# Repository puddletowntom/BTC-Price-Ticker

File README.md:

# Bitcoin Metrics Tracker

# WARNING!!

Problems still remain with this project when using Wi-Fi at the same time as LCD. Wi-Fi connection is inconsistent and sometimes fails a HTTP request. 
Another attempt was made in a different project where i failed to get Wi-Fi working at all with display. Both RGB display and Wi-Fi use PSRAM so there is a problem with shared resources. Getting around this may require a change to the hardware. I was thinking of simply using 2 ESP32s with 1 dedicated to RF. Perhaps there is a clever solution around temporarily disabling SPI bus for LCD on Wi-Fi commands or maybe some internal changes around LCD initialisation. Solving this problem has been too time consuming and a more careful design of the hardware would have been better I think. 

# Introduction

The Bitcoin metrics tracker was designed to sit near your desktop and keep an eye on several key important metrics on the Bitcoin network. These metrics include the Bitcoin price, the total Bitcoin marketcap, the total Bitcoin supply, the hash rate of the network, the current number of Bitcoins rewarded per block, the estimated time interval between blocks mined, the number of blocks mined so far and the remaining blocks left to mine in the current 4 year cycle. It uses Wi-Fi to connect to Blockchain.com to update the metrics at regular intervals. There is no need to hard code Wi-Fi credentials as there is a WPS setup for synchronisation with your router. Router credentials are then saved to flash memory via NVS so that you only have to do it one time. The green light on the screen indicates if Wi-Fi is connected. The green light will switch off if disconnected with the router. It will try to reconnect when it disconnects. The spinner around the green light is when the data is updating. 

# Parts Included

For the 3D printed case I have included the 3mf files. This project includes the following,

- RGB (565) display with ST7701s IC driver,
- ESP32-S3 R8 (8MB PSRAM) and 4MB of flash memory,
- Charging circuitry on PCB,
- USB-C,
- 3D print case

# Development Board

# Software 

- Kicad for PCB files,
- Fusion 360 for STL files,
- ESP-IDF for development environment,
- SquareLine Studio for display graphics

# Pinout

You can find the entire pinout with the schematic provided. But a brief overview is as follows,

Buttons

- TP6 to TP7 for Power button,
- SW3 - Reset button,
- SW4 - Boot button

# WPS

When you first turn on the device you will be met with the WPS screen. This is so you can connect to your router without needing to type your Wi-Fi credentials. So you need to press your WPS button on your router to sync it with the device. If it fails to move on from the WPS screen, unplug the device and plug it back in and press the WPS button on the router again. If it syncs with your router it will move on to the next screen which is a Bitcoin logo saying setup. 

# Programming the device

There are two modes for the ESP32-S3, download mode (upload program) and run mode (code running). To put the board in program mode press and hold the button SW4 (boot) and while this is still being held press the SW3 (reset) button. To put the board into run mode just press SW3 (reset) button once or alternatively just unplug the device. 

- idf.py set-target ESP32-S3 (only need to do this once)
- idf.py build (rebuild when you make changes to code)
- idf.py flash -p COM8 -b 921600 monitor (download code while monitoring)

# Restore credentials

If you want to change the Wi-Fi credentials to a new router, I have put in a define for restoring credentials. To do this you need to uncomment the following and build+download+run this code to clear credentials. 

#define CONFIG_RESTORE

You then need to comment it out again and download it to revert to original code. 

//#define CONFIG_RESTORE

# Further Work

The device currently doesnt have a GPIO reset button which means that once you sync the device with a Wi-Fi router via WPS you cant join a different router unless you reprogram the board with the config restore feature.

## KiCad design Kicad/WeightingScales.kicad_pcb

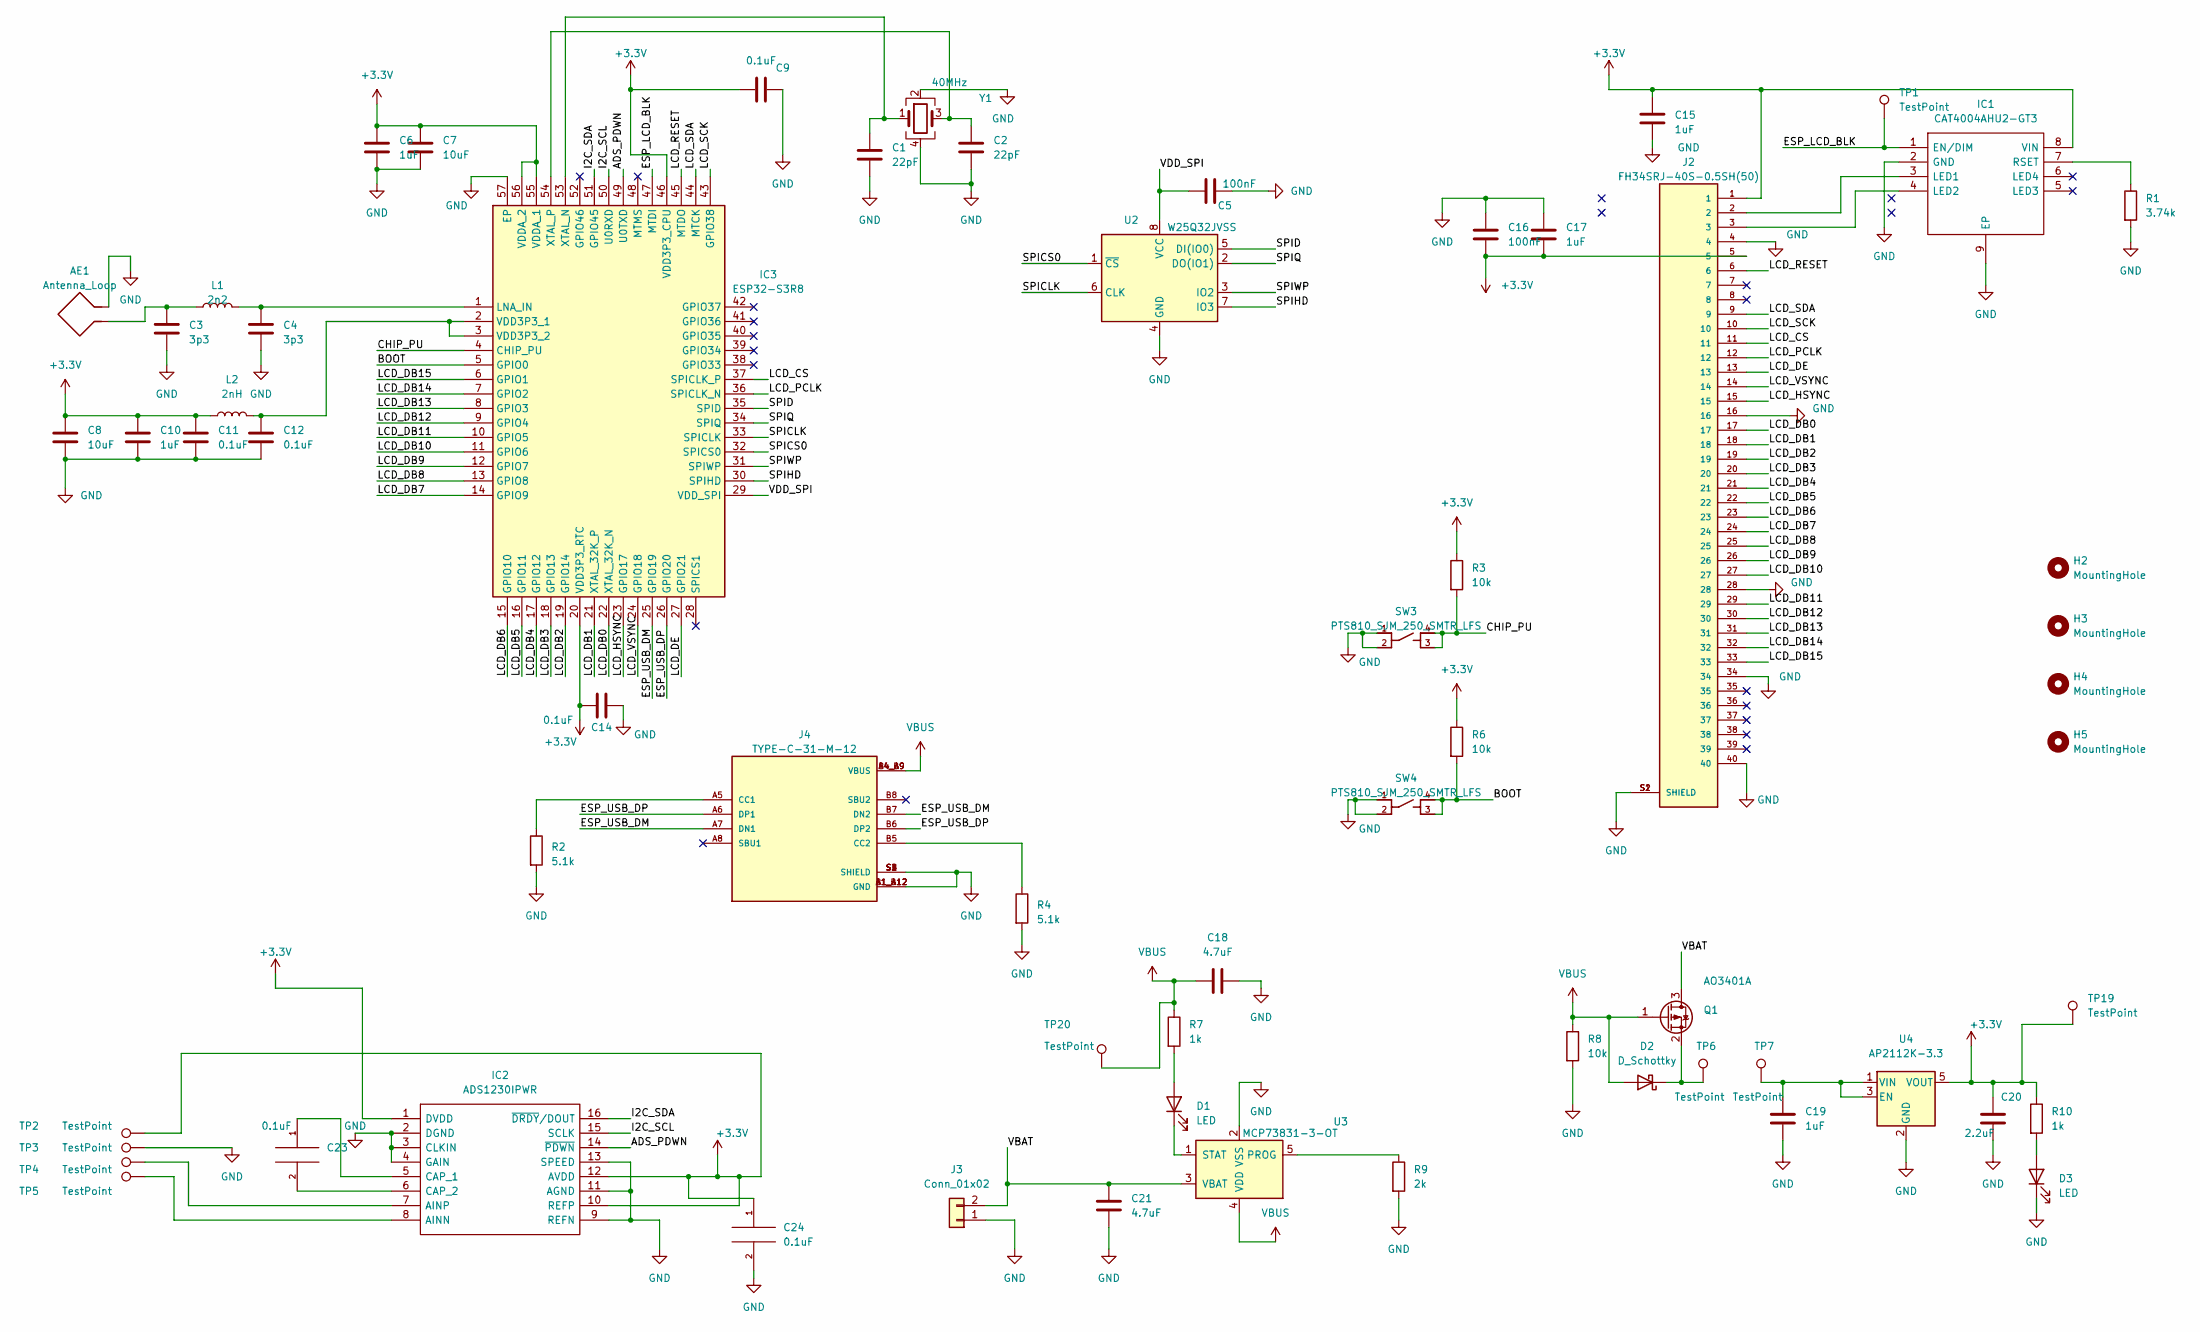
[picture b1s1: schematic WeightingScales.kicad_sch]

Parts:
AE1: Antenna_Loop; ESPRESSIF_ESP32_MIFA_2.4GHz_Right
C1, C2: 22pF; C_0402_1005Metric
C3, C4: 3p3; C_0402_1005Metric
C5, C16: 100nF; C_0402_1005Metric
C6, C10, C17, C19: 1uF; C_0402_1005Metric
C7, C8: 10uF; C_0603_1608Metric
C9, C11, C12, C14, C23, C24: 0.1uF; C_0402_1005Metric
C15: 1uF; C_0805_2012Metric
C18, C21: 4.7uF; C_0603_1608Metric
C20: 2.2uF; C_0402_1005Metric
D1, D3: LED; LED_0603_1608Metric
D2: D_Schottky; D_0603_1608Metric
H2, H3, H4, H5: MountingHole; MountingHole_2.2mm_M2
IC1: CAT4004AHU2-GT3; SON50P200X200X55-9N; Mouser Part Number 863-CAT4004AHU2-GT3
IC2: ADS1230IPWR; SOP65P640X120-16N; Mouser Part Number 595-ADS1230IPWR
IC3: ESP32-S3R8; QFN40P700X700X90-57N-D; Mouser Part Number 356-ESP32-S3R8
J2: FH34SRJ-40S-0.5SH(50); HRS_FH34SRJ-40S-0.5SH(50)
J3: Conn_01x02; JST_PH_S2B-PH-SM4-TB_1x02-1MP_P2.00mm_Horizontal
J4: TYPE-C-31-M-12; HRO_TYPE-C-31-M-12; PARTREV 2020.12.08
L1: 2n2; L_0402_1005Metric
L2: 2nH; L_0402_1005Metric
Q1: AO3401A; SOT-23
R1: 3.74k; R_0805_2012Metric
R2, R4: 5.1k; R_0805_2012Metric
R3, R6, R8: 10k; R_0805_2012Metric
R7, R10: 1k; R_0805_2012Metric
R9: 2k; R_0805_2012Metric
SW3, SW4: PTS810_SJM_250_SMTR_LFS; SW_PTS810_SJM_250_SMTR_LFS
TP1, TP2, TP3, TP4, TP5, TP6, TP7, TP19, TP20: TestPoint; Pin_D0.7mm_L6.5mm_W1.8mm_FlatFork
U2: W25Q32JVSS; SOIC-8_5.23x5.23mm_P1.27mm
U3: MCP73831-3-OT; SOT-23-5
U4: AP2112K-3.3; SOT-23-5
Y1: 40MHz; Crystal_SMD_3225-4Pin_3.2x2.5mm

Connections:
+3.3V: C6.1, C7.1, C8.1, C9.1, C10.1, C11.1, C14.1, C15.2, C16.2, C17.2, C20.1, C24.1, IC1.8 (VIN), IC2.1 (DVDD), IC2.10 (REFP), IC2.12 (AVDD), IC3.20 (VDD3P3_RTC), IC3.46 (VDD3P3_CPU), IC3.55 (VDDA_1), IC3.56 (VDDA_2), J2.1, J2.5, L2.1, R3.1, R6.1, R10.1, TP2.1, TP19.1, U4.5 (VOUT)
/ADS_PDWN: IC2.14 (~PDWN), IC3.49 (U0TXD)
/BOOT: IC3.5 (GPIO0), R6.2, SW4.3, SW4.4
/CHIP_PU: IC3.4 (CHIP_PU), R3.2, SW3.3, SW3.4
/ESP_LCD_BLK: IC1.1 (EN/DIM), IC3.47 (MTDI), TP1.1
/ESP_USB_DM: IC3.25 (GPIO19), J4.A7 (DN1), J4.B7 (DN2)
/ESP_USB_DP: IC3.26 (GPIO20), J4.A6 (DP1), J4.B6 (DP2)
/I2C_SCL: IC2.15 (SCLK), IC3.50 (U0RXD)
/I2C_SDA: IC2.16 (~DRDY/DOUT), IC3.51 (GPIO45)
/LCD_CS: IC3.37 (SPICLK_P), J2.11
/LCD_DB0: IC3.22 (XTAL_32K_N), J2.17
/LCD_DB1: IC3.21 (XTAL_32K_P), J2.18
/LCD_DB2: IC3.19 (GPIO14), J2.19
/LCD_DB3: IC3.18 (GPIO13), J2.20
/LCD_DB4: IC3.17 (GPIO12), J2.21
/LCD_DB5: IC3.16 (GPIO11), J2.22
/LCD_DB6: IC3.15 (GPIO10), J2.23
/LCD_DB7: IC3.14 (GPIO9), J2.24
/LCD_DB8: IC3.13 (GPIO8), J2.25
/LCD_DB9: IC3.12 (GPIO7), J2.26
/LCD_DB10: IC3.11 (GPIO6), J2.27
/LCD_DB11: IC3.10 (GPIO5), J2.29
/LCD_DB12: IC3.9 (GPIO4), J2.30
/LCD_DB13: IC3.8 (GPIO3), J2.31
/LCD_DB14: IC3.7 (GPIO2), J2.32
/LCD_DB15: IC3.6 (GPIO1), J2.33
/LCD_DE: IC3.27 (GPIO21), J2.13
/LCD_HSYNC: IC3.23 (GPIO17), J2.15
/LCD_PCLK: IC3.36 (SPICLK_N), J2.12
/LCD_RESET: IC3.45 (MTDO), J2.6
/LCD_SCK: IC3.43 (GPIO38), J2.10
/LCD_SDA: IC3.44 (MTCK), J2.9
/LCD_VSYNC: IC3.24 (GPIO18), J2.14
/SPICLK: IC3.33 (SPICLK), U2.6 (CLK)
/SPICS0: IC3.32 (SPICS0), U2.1 (~CS)
/SPID: IC3.35 (SPID), U2.5 (DI(IO0))
/SPIHD: IC3.30 (SPIHD), U2.7 (IO3)
/SPIQ: IC3.34 (SPIQ), U2.2 (DO(IO1))
/SPIWP: IC3.31 (SPIWP), U2.3 (IO2)
/VBAT: C21.1, J3.2, Q1.3 (D), U3.3 (VBAT)
/VDD_SPI: C5.1, IC3.29 (VDD_SPI), U2.8 (VCC)
GND: AE1.2, C1.2, C2.2, C3.2, C4.2, C5.2, C6.2, C7.2, C8.2, C9.2, C10.2, C11.2, C12.2, C14.2, C15.1, C16.1, C17.1, C18.2, C19.2, C20.2, C21.2, C24.2, D3.1 (K), IC1.2 (GND), IC1.9 (EP), IC2.2 (DGND), IC2.3 (CLKIN), IC2.4 (GAIN), IC2.9 (REFN), IC2.11 (AGND), IC2.13 (SPEED), IC3.57 (EP), J2.4, J2.16, J2.28, J2.34, J2.40, J2.S1 (SHIELD), J2.S2 (SHIELD), J3.1, J4.A1_B12 (GND), J4.B1_A12 (GND), J4.S1 (SHIELD), J4.S2 (SHIELD), J4.S3 (SHIELD), J4.S4 (SHIELD), R1.2, R2.2, R4.2, R8.2, R9.2, SW3.1, SW3.2, SW4.1, SW4.2, TP3.1, U2.4 (GND), U3.2 (VSS), U4.2 (GND), Y1.2, Y1.4; also elsewhere on the board
unnamed 42: AE1.1, C3.1, L1.1; also elsewhere on the board
unnamed: D1.2 (A), R7.2
unnamed: D1.1 (K), U3.1 (STAT)
unnamed: D2.1 (K), Q1.2 (S), TP6.1
unnamed: D3.2 (A), R10.2
unnamed: IC1.3 (LED1), J2.2
unnamed: IC1.4 (LED2), J2.3
unnamed: IC1.7 (RSET), R1.1
unnamed: IC2.8 (AINN), TP5.1
unnamed: IC2.7 (AINP), TP4.1
unnamed: C23.1, IC2.5 (CAP_1)
unnamed: C23.2, IC2.6 (CAP_2)
unnamed: C4.1, IC3.1 (LNA_IN), L1.2
unnamed: C12.1, IC3.2 (VDD3P3_1), IC3.3 (VDD3P3_2), L2.2
unnamed: C1.1, IC3.53 (XTAL_N), Y1.1
unnamed: C2.1, IC3.54 (XTAL_P), Y1.3
unnamed: J4.A5 (CC1), R2.1
unnamed: J4.B5 (CC2), R4.1
unnamed: R9.1, U3.5 (PROG)
unnamed: C19.1, TP7.1, U4.1 (VIN), U4.3 (EN)
VBUS: C18.1, D2.2 (A), J4.A4_B9 (VBUS), J4.B4_A9 (VBUS), Q1.1 (G), R7.1, R8.1, TP20.1, U3.4 (VDD)

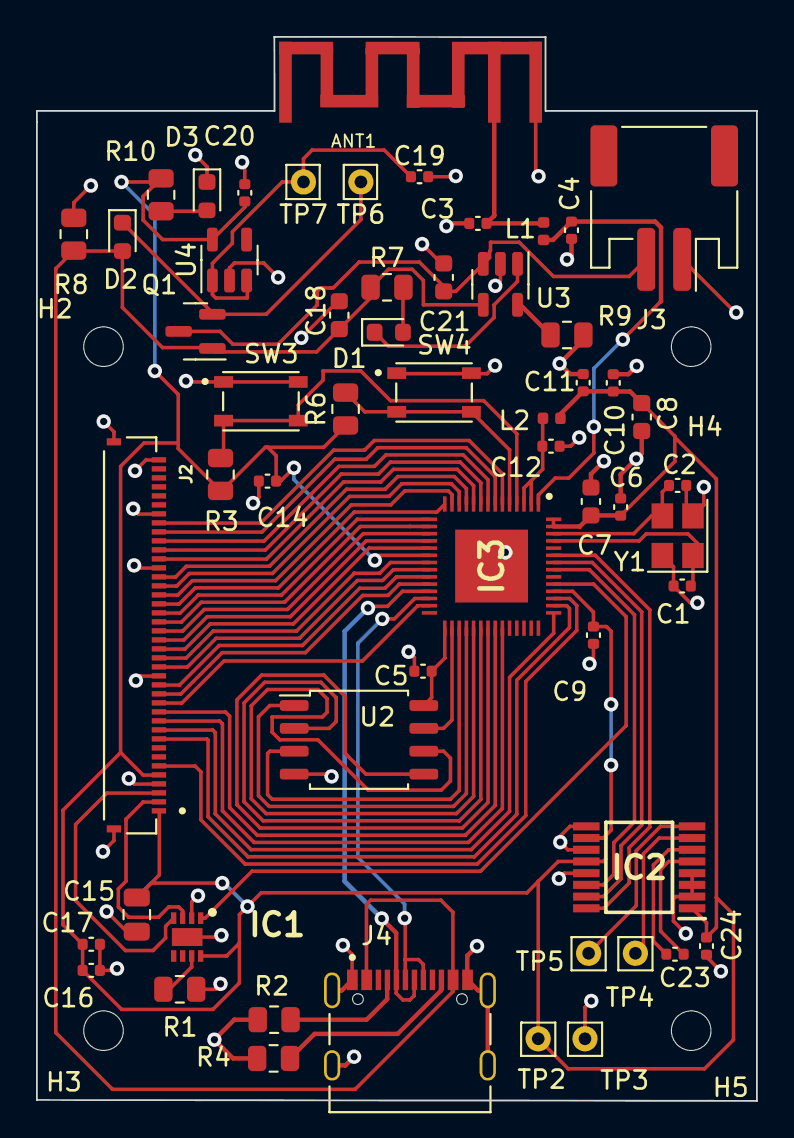
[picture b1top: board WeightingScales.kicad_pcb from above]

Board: 2 copper layers, 40.0 x 59.1 mm, 60 parts (0 on the bottom side), 63 nets.

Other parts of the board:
ANT1: PCB_ANT; PCB_Antenna_2_4_GHz_ESP32

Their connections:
GND: ANT1.2; also elsewhere on the board
unnamed 42: ANT1.1; also elsewhere on the board

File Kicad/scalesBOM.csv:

"Source:","C:\Users\ronan\Documents\KiCad\WSUpgrade\WeightingScales.kicad_sch"
"Date:","10/06/2023 12:21:17"
"Tool:","Eeschema 7.0.1"
"Generator:","C:\Program Files\KiCad\7.0\bin\scripting\plugins/bom_csv_grouped_by_value_with_fp.py"
"Component Count:","63"
"Ref","Qnty","Value","Cmp name","Footprint","Description","Vendor","DNP"
"AE1","1","Antenna_Loop","Antenna_Loop","ESP_Antenna:ESPRESSIF_ESP32_MIFA_2.4GHz_Right","Loop antenna","",""
"C1, C2","2","22pF","C","Capacitor_SMD:C_0402_1005Metric","Unpolarized capacitor","",""
"C3, C4","2","3p3","C","Capacitor_SMD:C_0402_1005Metric","Unpolarized capacitor","",""
"C5, C16","2","100nF","C","Capacitor_SMD:C_0402_1005Metric","Unpolarized capacitor","",""
"C6, C10, C17, C19","4","1uF","C","Capacitor_SMD:C_0402_1005Metric","Unpolarized capacitor","",""
"C7, C8","2","10uF","C","Capacitor_SMD:C_0603_1608Metric","Unpolarized capacitor","",""
"C9, C11, C12, C14, C23, C24","6","0.1uF","C","Capacitor_SMD:C_0402_1005Metric","Capacitor symbol for simulation only","",""
"C15","1","1uF","C","Capacitor_SMD:C_0805_2012Metric","Unpolarized capacitor","",""
"C18, C21","2","4.7uF","C","Capacitor_SMD:C_0603_1608Metric","Unpolarized capacitor","",""
"C20","1","2.2uF","C","Capacitor_SMD:C_0402_1005Metric","Unpolarized capacitor","",""
"D1, D3","2","LED","LED","LED_SMD:LED_0603_1608Metric","Light emitting diode","",""
"D2","1","D_Schottky","D_Schottky","Diode_SMD:D_0603_1608Metric","Schottky diode","",""
"H2, H3, H4, H5","4","MountingHole","MountingHole","MountingHole:MountingHole_2.2mm_M2","Mounting Hole without connection","",""
"IC1","1","CAT4004AHU2-GT3","CAT4004AHU2-GT3","CAT4004A-libraries:SON50P200X200X55-9N","Driver,LED,4-channel,EZDim,UDFN8 ON Semiconductor CAT4004AHU2-GT3, LED Display Driver, 4 V, 8-Pin UDFN","",""
"IC2","1","ADS1230IPWR","ADS1230IPWR","ADS1230IPWR:SOP65P640X120-16N","20-Bit, 80SPS, 1-Ch Delta-Sigma ADC for Resistive Bridge Sensors & Weigh Scales","",""
"IC3","1","ESP32-S3R8","ESP32-S3R8","ESP32-S3R8:QFN40P700X700X90-57N-D","WiFi Modules - 802.11 SMD IC, Dual-Core MCU, Wi-Fi 2.4G & BLE 5.0 Combo, 8 MB Octal SPI PSRAM, QFN 56-pin, 7*7 mm","",""
"J2","1","FH34SRJ-40S-0.5SH(50)","FH34SRJ-40S-0.5SH(50)","FH34SRJ-40S-0.5SH_50_:HRS_FH34SRJ-40S-0.5SH(50)","","",""
"J3","1","Conn_01x02","Conn_01x02","Connector_JST:JST_PH_S2B-PH-SM4-TB_1x02-1MP_P2.00mm_Horizontal","Generic connector, single row, 01x02, script generated (kicad-library-utils/schlib/autogen/connector/)","",""
"J4","1","TYPE-C-31-M-12","TYPE-C-31-M-12","TYPE-C-31-M-12:HRO_TYPE-C-31-M-12","","",""
"L1","1","2n2","L","Inductor_SMD:L_0402_1005Metric","Inductor","",""
"L2","1","2nH","L","Inductor_SMD:L_0402_1005Metric","Inductor","",""
"Q1","1","AO3401A","AO3401A","Package_TO_SOT_SMD:SOT-23","-4.0A Id, -30V Vds, P-Channel MOSFET, SOT-23","",""
"R1","1","3.74k","R","Resistor_SMD:R_0805_2012Metric","Resistor","",""
"R2, R4","2","5.1k","R","Resistor_SMD:R_0805_2012Metric","Resistor","",""
"R3, R6, R8","3","10k","R","Resistor_SMD:R_0805_2012Metric","Resistor","",""
"R7, R10","2","1k","R","Resistor_SMD:R_0805_2012Metric","Resistor","",""
"R9","1","2k","R","Resistor_SMD:R_0805_2012Metric","Resistor","",""
"SW3, SW4","2","PTS810_SJM_250_SMTR_LFS","PTS810_SJM_250_SMTR_LFS","PTS810_SJM_250_SMTR_LFS:SW_PTS810_SJM_250_SMTR_LFS","","",""
"TP1, TP2, TP3, TP4, TP5, TP6, TP7, TP19, TP20","9","TestPoint","TestPoint","Connector_Pin:Pin_D0.7mm_L6.5mm_W1.8mm_FlatFork","test point","",""
"U2","1","W25Q32JVSS","W25Q32JVSS","Package_SO:SOIC-8_5.23x5.23mm_P1.27mm","32Mb Serial Flash Memory, Standard/Dual/Quad SPI, SOIC-8","",""
"U3","1","MCP73831-3-OT","MCP73831-3-OT","Package_TO_SOT_SMD:SOT-23-5","Single cell, Li-Ion/Li-Po charge management controller, 4.35V, Tri-State Status Output, in SOT23-5 package","",""
"U4","1","AP2112K-3.3","AP2112K-3.3","Package_TO_SOT_SMD:SOT-23-5","600mA low dropout linear regulator, with enable pin, 3.8V-6V input voltage range, 3.3V fixed positive output, SOT-23-5","",""
"Y1","1","40MHz","Crystal_GND24","Crystal:Crystal_SMD_3225-4Pin_3.2x2.5mm","Four pin crystal, GND on pins 2 and 4","",""

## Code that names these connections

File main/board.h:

#pragma once

// RGB SPI interface
#define LCD_SPI_DATA0     39  /*!< for 1-line SPI, this also refered as MOSI */
#define LCD_SPI_CLK       38
#define LCD_SPI_CS        47
#define LCD_SPI_DC        -1
#define LCD_SPI_RST       40

// RGB interface
#define LCD_PCLK_GPIO     (48)
#define LCD_VSYNC_GPIO    (18)
#define LCD_HSYNC_GPIO    (17)
#define LCD_DE_GPIO       (21)

#define RGB_B0       (16)  // B0
#define RGB_B1       (15)  // B1
#define RGB_B2       (14)   // B2
#define RGB_B3       (13)  // B3
#define RGB_B4       (12)  // B4
#define RGB_G0       (11)   // G0
#define RGB_G1       (10)  // G1
#define RGB_G2       (9)  // G2
#define RGB_G3       (8)  // G3
#define RGB_G4       (7)  // G4
#define RGB_G5      (6)  // G5
#define RGB_R0      (5)  // R0
#define RGB_R1      (4)  // R1
#define RGB_R2      (3)   // R2
#define RGB_R3      (2)  // R3
#define RGB_R4      (1)  // R4

#define LCD_DATA0_GPIO    (RGB_B0)   // B0
#define LCD_DATA1_GPIO    (RGB_B1)   // B1
#define LCD_DATA2_GPIO    (RGB_B2)   // B2
#define LCD_DATA3_GPIO    (RGB_B3)   // B3
#define LCD_DATA4_GPIO    (RGB_B4)   // B4
#define LCD_DATA5_GPIO    (RGB_G0)   // G0
#define LCD_DATA6_GPIO    (RGB_G1)    // G1
#define LCD_DATA7_GPIO    (RGB_G2)   // G2
#define LCD_DATA8_GPIO    (RGB_G3)   // G3
#define LCD_DATA9_GPIO    (RGB_G4)   // G4
#define LCD_DATA10_GPIO   (RGB_G5)   // G5
#define LCD_DATA11_GPIO   (RGB_R0)   // R0
#define LCD_DATA12_GPIO   (RGB_R1)    // R1
#define LCD_DATA13_GPIO   (RGB_R2)    // R2
#define LCD_DATA14_GPIO   (RGB_R3)    // R3
#define LCD_DATA15_GPIO   (RGB_R4)    // R4
#define LCD_DISP_EN_GPIO  (-1)

#define LCD_PIN_BK_LIGHT       41

#define LCD_BK_LIGHT_ON_LEVEL  1
#define LCD_BK_LIGHT_OFF_LEVEL !LCD_BK_LIGHT_ON_LEVEL

//#define ENCODER_A_PIN     (5)
//#define ENCODER_B_PIN     (6)

//#define MOTOR_PIN         (7)
//#define LED_PIN           (4)

//#define BTN_PIN           (3)

//#define EXT_PIN_0         (1)
//#define EXT_PIN_1         (2)
//#define EXT_PIN_2         (20)
//#define EXT_PIN_3         (19)

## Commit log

2023-08-10 BTC price ticker for round display
2023-08-11 Images for BTC logo and Wi-Fi logo
2023-08-12 Enabled toggling wifi logo with connection
2023-08-18 Added various Bitcoin stats from blockchain api
2023-08-21 Stats screen operational with real values
2023-09-13 WPS code added but not tested
2023-09-14 Edge case for WPS if stored config fails run WPS
2023-09-15 Better presentation for metrics
2023-09-15 Using the metrics i actually want to see
2023-09-18 Better stats being displayed with better format
2023-09-19 Commas put in to numbers for better readability
2023-09-19 missed file with older commit
2023-09-19 Exahash suffix added
2023-09-21 Added Wi-Fi connection indicator and spindle for requests
2023-09-22 Included a setup screen so that the its presented better before loading. If fails it will go to main screen after a few attempts anyway
2023-09-22 Better use of WPS and connection
2023-09-23 Using WPS on every startup with an initial 10s wait screen
2023-09-26 Better btc price ticker used (faster updating), fixed bug WPS (starts on first try rather than two tries)
2023-09-27 Clear screen when you get radio activity so that nvs doesnt shift screen
2023-09-27 wifi deinit added when deleting credentials for proper restore
2023-09-28 Bounce buffer put back in with changed coordinates for display.
2023-10-04 Clean up
2023-10-05 Remove my_data.h
2023-10-05 update to the README file
2023-10-05 update to README
2023-10-11 f3d file added
2024-03-05 experiment with locking lvgl for better wifi performance
2024-03-06 Problems in readme
2024-03-12 Some improvemnets around wifi
